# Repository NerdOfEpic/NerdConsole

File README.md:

# NerdConsole

For now, just some breadboard helper PCBs.  Enjoy.  :)

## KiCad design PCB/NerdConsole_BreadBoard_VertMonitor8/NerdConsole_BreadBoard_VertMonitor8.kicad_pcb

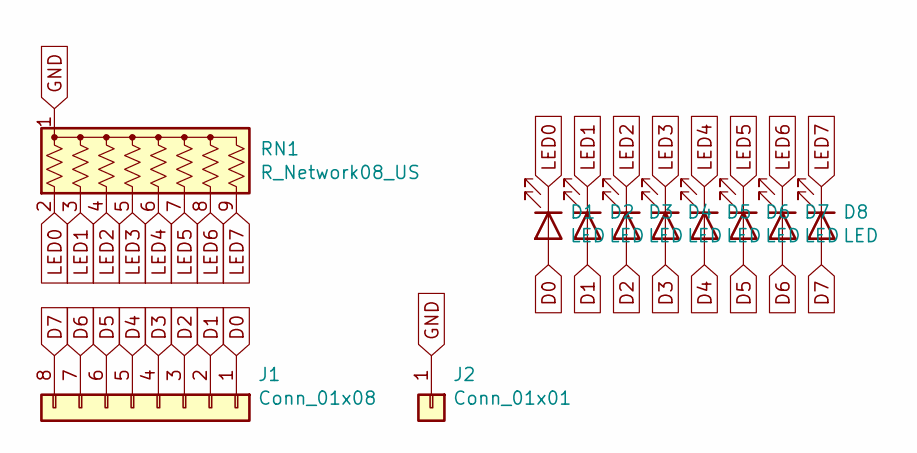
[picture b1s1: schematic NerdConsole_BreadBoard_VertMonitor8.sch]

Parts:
D1, D2, D3, D4, D5, D6, D7, D8: LED; LED_0805_2012Metric_Pad1.15x1.40mm_HandSolder
J1: Conn_01x08; PinHeader_1x08_P2.54mm_Horizontal
J2: Conn_01x01; PinSocket_1x01_P2.54mm_Horizontal
RN1: R_Network08_US; R_Array_SIP9

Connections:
D0: D1.2 (A), J1.1
D1: D2.2 (A), J1.2
D2: D3.2 (A), J1.3
D3: D4.2 (A), J1.4
D4: D5.2 (A), J1.5
D5: D6.2 (A), J1.6
D6: D7.2 (A), J1.7
D7: D8.2 (A), J1.8
GND: J2.1, RN1.1 (common)
LED0: D1.1 (K), RN1.2 (R1)
LED1: D2.1 (K), RN1.3 (R2)
LED2: D3.1 (K), RN1.4 (R3)
LED3: D4.1 (K), RN1.5 (R4)
LED4: D5.1 (K), RN1.6 (R5)
LED5: D6.1 (K), RN1.7 (R6)
LED6: D7.1 (K), RN1.8 (R7)
LED7: D8.1 (K), RN1.9 (R8)

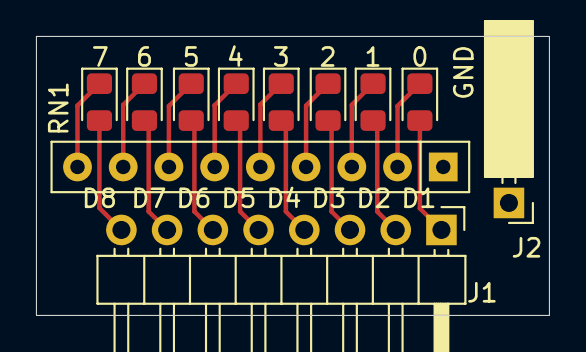
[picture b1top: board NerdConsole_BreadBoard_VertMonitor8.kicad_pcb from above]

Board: 2 copper layers, 28.5 x 15.5 mm, 11 parts (0 on the bottom side), 17 nets.

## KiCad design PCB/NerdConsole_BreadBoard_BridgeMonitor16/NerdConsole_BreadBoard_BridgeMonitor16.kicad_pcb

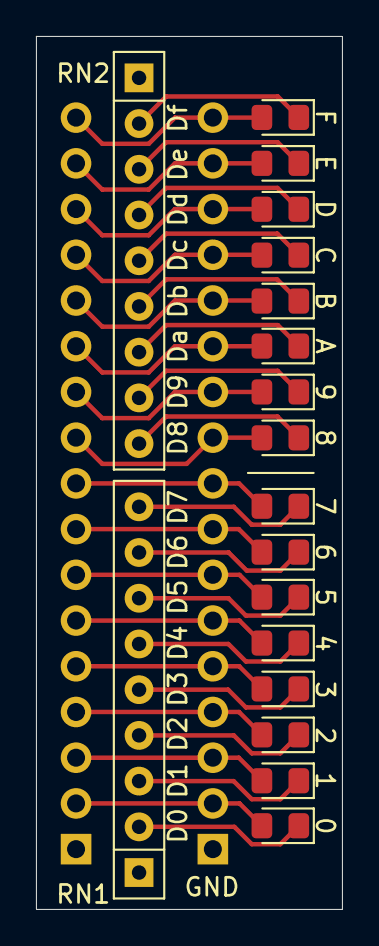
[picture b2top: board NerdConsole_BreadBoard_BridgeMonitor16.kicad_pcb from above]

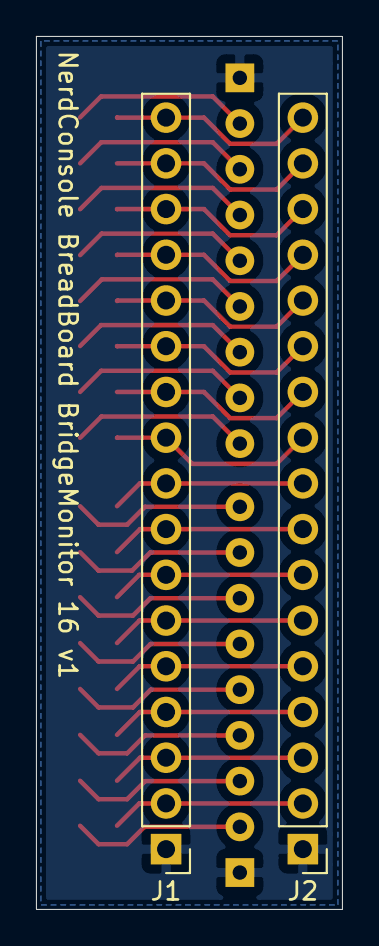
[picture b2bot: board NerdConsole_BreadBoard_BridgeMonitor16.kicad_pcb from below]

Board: 2 copper layers, 17.0 x 48.5 mm, 20 parts (2 on the bottom side), 33 nets.

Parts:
D0, D1, D2, D3, D4, D5, D6, D7, D8, D9: LED; LED_0805_2012Metric_Pad1.15x1.40mm_HandSolder
Da: LED; LED_0805_2012Metric_Pad1.15x1.40mm_HandSolder
Db: LED; LED_0805_2012Metric_Pad1.15x1.40mm_HandSolder
Dc: LED; LED_0805_2012Metric_Pad1.15x1.40mm_HandSolder
Dd: LED; LED_0805_2012Metric_Pad1.15x1.40mm_HandSolder
De: LED; LED_0805_2012Metric_Pad1.15x1.40mm_HandSolder
Df: LED; LED_0805_2012Metric_Pad1.15x1.40mm_HandSolder
J1, J2: Conn_01x17; PinHeader_1x17_P2.54mm_Vertical
RN1, RN2: R_Network08_US; R_Array_SIP9

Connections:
D0: D0.2, J1.2, J2.2
D1: D1.2, J1.3, J2.3
D2: D2.2, J1.4, J2.4
D3: D3.2, J1.5, J2.5
D4: D4.2, J1.6, J2.6
D5: D5.2, J1.7, J2.7
D6: D6.2, J1.8, J2.8
D7: D7.2, J1.9, J2.9
D8: D8.2, J1.10, J2.10
D9: D9.2, J1.11, J2.11
D10: Da.2, J1.12, J2.12
D11: Db.2, J1.13, J2.13
D12: Dc.2, J1.14, J2.14
D13: Dd.2, J1.15, J2.15
D14: De.2, J1.16, J2.16
D15: Df.2, J1.17, J2.17
GND: J1.1, J2.1, RN1.1, RN2.1
LED0: D0.1, RN1.2
LED1: D1.1, RN1.3
LED2: D2.1, RN1.4
LED3: D3.1, RN1.5
LED4: D4.1, RN1.6
LED5: D5.1, RN1.7
LED6: D6.1, RN1.8
LED7: D7.1, RN1.9
LED8: D8.1, RN2.9
LED9: D9.1, RN2.8
LED10: Da.1, RN2.7
LED11: Db.1, RN2.6
LED12: Dc.1, RN2.5
LED13: Dd.1, RN2.4
LED14: De.1, RN2.3
LED15: Df.1, RN2.2

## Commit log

2021-02-04 Added breadboard helper PCBs.
2021-02-04 Added vertical (non-bridging) monitor board.
2021-02-04 Renamed Monitor to BridgeMonitor and made a new free standing Monitor.
2021-02-04 Added NerdConsole labelling and a couple more boards.
